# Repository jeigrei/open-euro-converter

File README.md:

## open-euro-converter

__euro-converter__ is a 12hp eurorack module for interfacing multiple eurorack modular synth signals with traditional audio equipment that wants 1/4" TS inputs. Each of its five channels features an inline potentiometer for attenuating the signal from eurorack-levels to studio-levels. Since euro-converter is completely passive, it also works in reverse to easily bring 1/4" outputs into 3.5mm eurorack-friendly inputs!

## What's included
* __bom.xlsx__ - The bill of materials lists the components (other than the PCB and faceplate) you'll need to fabricate one yourself.
* __kicad__ - The original project files, if you want to tweak euro-converter to your liking.
* __GERBERS__ - The GERBER files to send to the PCB fab ([OshPark is good!](https://oshpark.com/)), if you like euro-converter the way it is.
* __3d__ - STL files to 3D-print a faceplate. There's a complete model as well as one split into two pieces for use with printers featuring smaller build stages.

## Instructions

#### Get your hands on the components

Walk through the process at OshPark (or your fab of choice) with the included GERBER files to get the PCB ordered. While you're waiting on the PCB fairy to visit, order the components from __bom.xlsx__ and print out/acquire a faceplate.

#### Place PCB components

Before you heat up the iron, place the 3.5mm jacks and pots on the board and put the faceplate over them. We want to make sure the faceplate fits while the components can still wiggle around a bit.

#### Solder PCB components

Now that everything's snug, solder your 3.5mm jacks, pots, and terminals to the board. Jacks and pots on the front, terminals on the back.

#### Solder wires to your 1/4" jacks

This is easier to do without having them attached to anything. For the wires, I recommend 18 AWG speaker wire. I used [this stuff](https://www.amazon.com/gp/product/B07CWPTHYH/ref=ppx_yo_dt_b_search_asin_title?ie=UTF8&th=1) from Amazon. Tip is signal, sleeve is ground, so by convention if you have red/black speaker wire, put the red on the tip lead.

#### Attach 1/4" wires to terminals and put it all together

The signal wire (red wire) goes to the terminal slot with the SQUARE pad. The ground wire goes to the slot with the CIRCLE pad. Once you're wired up, fasten the jacks to the faceplate with nuts.

All together, you should be looking at something that looks like this:

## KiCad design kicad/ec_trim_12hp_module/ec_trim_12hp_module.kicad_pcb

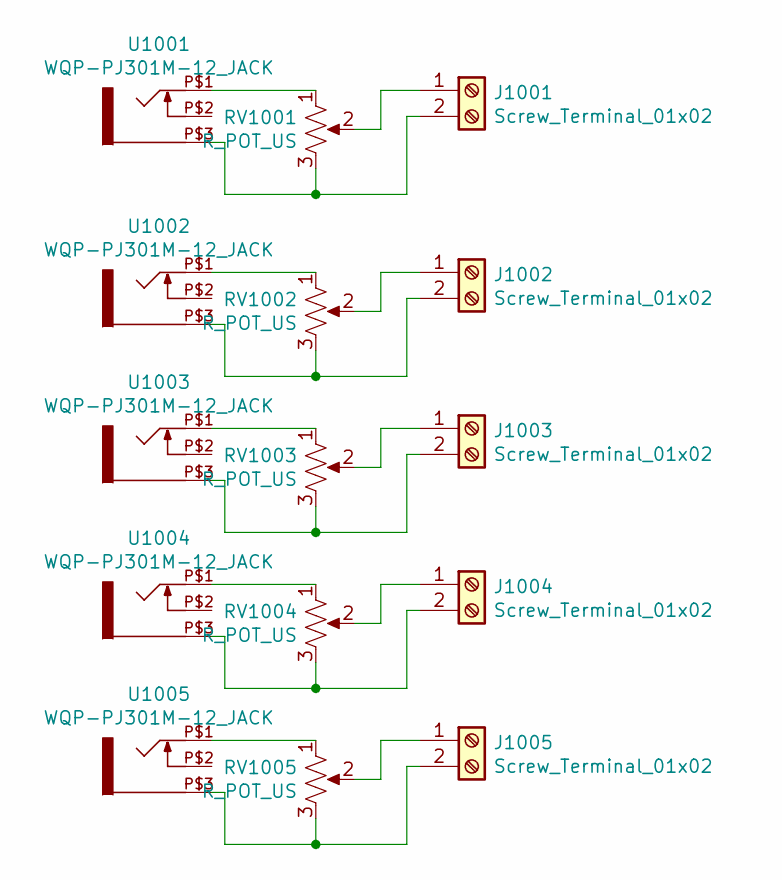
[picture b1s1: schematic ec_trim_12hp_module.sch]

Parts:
J1001, J1002, J1003, J1004, J1005: Screw_Terminal_01x02; TerminalBlock_bornier-2_P5.08mm
RV1001, RV1002, RV1003, RV1004, RV1005: R_POT_US; Thonk_9mm_TrimPot
U1001, U1002, U1003, U1004, U1005: WQP-PJ301M-12_JACK

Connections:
unnamed: J1001.1, RV1001.2
unnamed: J1001.2, RV1001.3, U1001.P$3 (1)
unnamed: J1002.1, RV1002.2
unnamed: J1002.2, RV1002.3, U1002.P$3 (1)
unnamed: J1003.1, RV1003.2
unnamed: J1003.2, RV1003.3, U1003.P$3 (1)
unnamed: J1004.1, RV1004.2
unnamed: J1004.2, RV1004.3, U1004.P$3 (1)
unnamed: J1005.1, RV1005.2
unnamed: J1005.2, RV1005.3, U1005.P$3 (1)
unnamed: RV1001.1, U1001.P$1 (2)
unnamed: RV1002.1, U1002.P$1 (2)
unnamed: RV1003.1, U1003.P$1 (2)
unnamed: RV1004.1, U1004.P$1 (2)
unnamed: RV1005.1, U1005.P$1 (2)

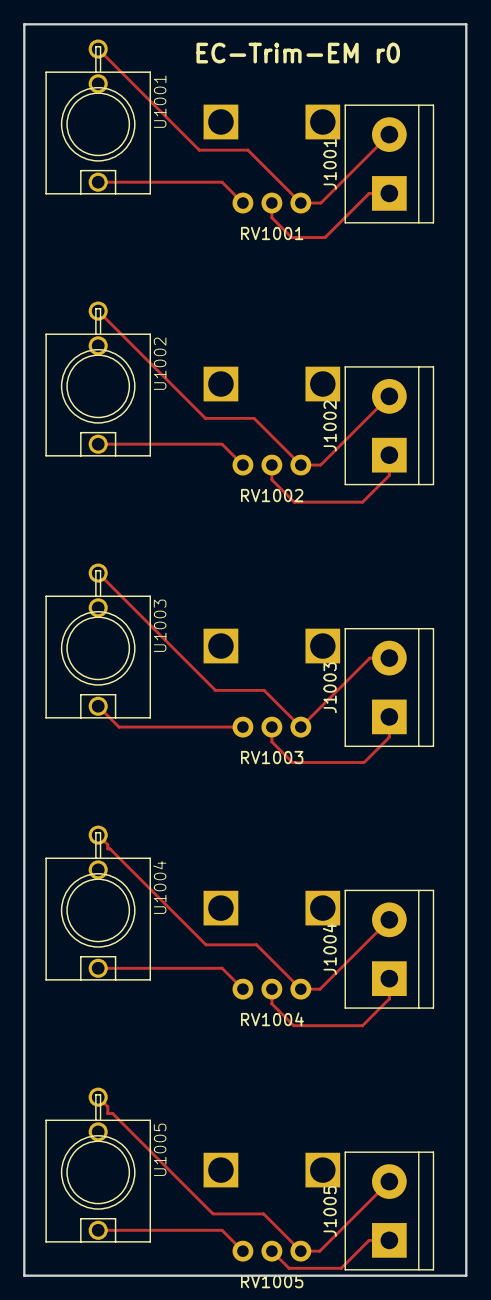
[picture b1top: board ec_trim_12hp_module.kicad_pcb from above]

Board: 2 copper layers, 38.2 x 108.1 mm, 15 parts (0 on the bottom side), 15 nets.

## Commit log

2020-11-24 dump project
2020-11-24 add split faceplate stls
